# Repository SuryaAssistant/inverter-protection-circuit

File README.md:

# inverter-protection-circuit
48V inverter protection circuit

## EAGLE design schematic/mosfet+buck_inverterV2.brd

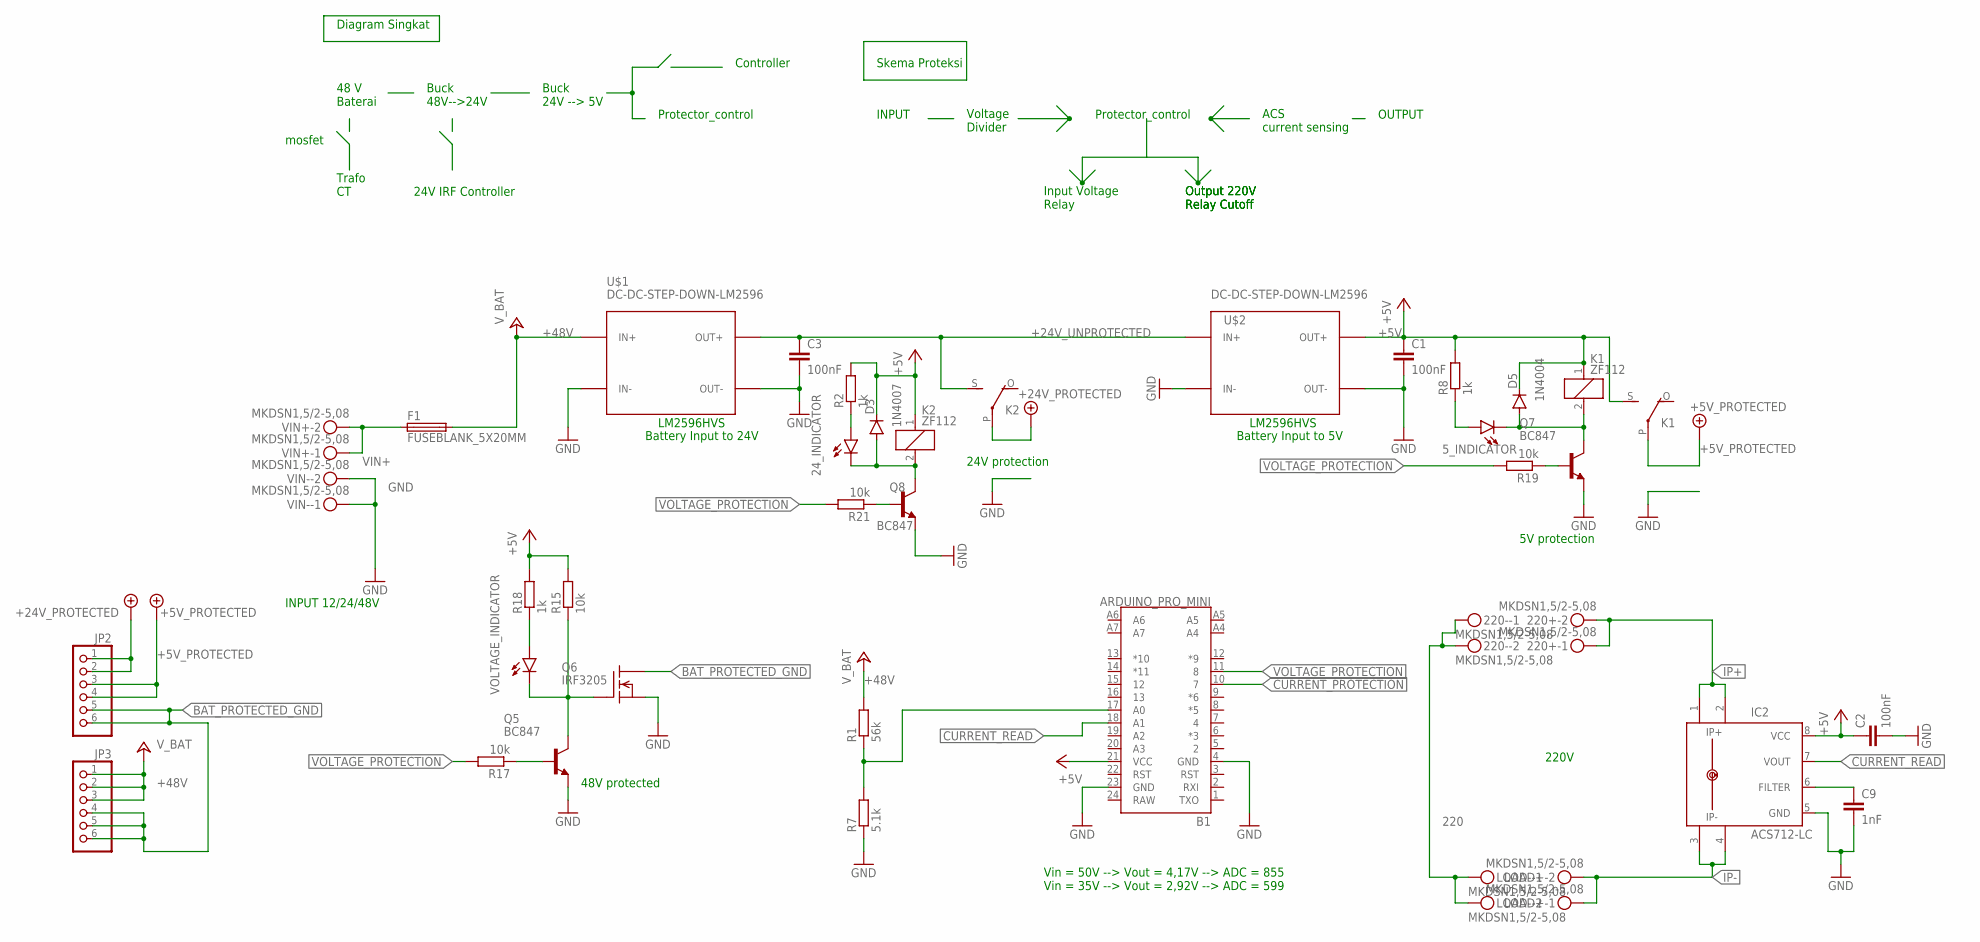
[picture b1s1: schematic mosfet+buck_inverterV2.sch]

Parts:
5_INDICATOR, 24_INDICATOR: LED1206; LED-1206
220+, 220-: MKDSN1,5/2-5,08
B1: ARDUINO_PRO_MINI
C1, C2, C3: 100nF; C0805K
C9: 1nF; C0805K
D3: 1N4007; DO41-10
D5: 1N4004; DO41-10
F1: FUSEBLANK_5X20MM; FUSE_HOLDER_5X20MM
IC2: ACS712-LC; SOIC8
JP2, JP3: PINHD-1X6CLEAN; 1X06-CLEAN
K1, K2: ZF112
LOAD+: MKDSN1,5/2-5,08
LOAD-: MKDSN1,5/2-5,08
Q5, Q7, Q8: BC847; SOT23
Q6: IRF3205; TO220
R1: 56k; R0805
R2, R8, R18: 1k; R0805
R7: 5.1k; R0805
R15, R17, R19, R21: 10k; R0805
U$1, U$2: DC-DC-STEP-DOWN-LM2596
VIN+: MKDSN1,5/2-5,08
VIN-: MKDSN1,5/2-5,08
VOLTAGE_INDICATOR: LED1206; LED-1206

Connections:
220: 220-.1, 220-.2, LOAD-.1, LOAD-.2
+5V: B1.21 (VCC), C1.1, C2.1, D3.C, D5.C, IC2.8 (VCC), K1.1, K1.S, K2.1, R2.2, R8.2, R15.2, R18.2, U$2.OUT+
+5V_PROTECTED: JP2.3, JP2.4, K1.P
+24V: JP2.1, JP2.2, K2.P
+24V_UNPROTECTED: C3.1, K2.S, U$1.OUT+, U$2.IN+
+48V: F1.2, JP3.1, JP3.2, JP3.3, R1.2, U$1.IN+
BAT_PROTECTED_GND: JP2.5, JP2.6, JP3.4, JP3.5, JP3.6, Q6.2 (D)
CURRENT_PROTECTION: B1.10 (7)
CURRENT_READ: B1.18 (A1), IC2.7 (VOUT)
GND: B1.4 (GND), B1.23 (GND), C1.2, C2.2, C3.2, C9.2, IC2.5 (GND), Q5.2 (E), Q6.3 (S), Q7.2 (E), Q8.2 (E), R7.1, U$1.IN-, U$1.OUT-, U$2.IN-, U$2.OUT-, VIN-.1, VIN-.2
IP+: 220+.1, 220+.2, IC2.1 (IP+), IC2.2 (IP+1)
IP-: IC2.3 (IP-), IC2.4 (IP-1), LOAD+.1, LOAD+.2
unnamed: B1.17 (A0), R1.1, R7.2
unnamed: 24_INDICATOR.A, R2.1
unnamed: Q5.3 (C), Q6.1 (G), R15.1, VOLTAGE_INDICATOR.C
unnamed: Q5.1 (B), R17.1
unnamed: 24_INDICATOR.C, D3.A, K2.2, Q8.3 (C)
unnamed: R18.1, VOLTAGE_INDICATOR.A
unnamed: 5_INDICATOR.C, D5.A, K1.2, Q7.3 (C)
unnamed: Q7.1 (B), R19.1
unnamed: Q8.1 (B), R21.1
unnamed: C9.1, IC2.6 (FILTER)
unnamed: 5_INDICATOR.A, R8.1
RAW: B1.24 (RAW)
VIN+: F1.1, VIN+.1, VIN+.2
VOLTAGE_PROTECTION: B1.11 (8), R17.2, R19.2, R21.2

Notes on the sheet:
INPUT 12/24/48V
Battery Input to 5V
LM2596HVS
Battery Input to 24V
Vin = 50V --> Vout = 4,17V --> ADC = 855 Vin = 35V --> Vout = 2,92V --> ADC = 599
48V protected
24V protection
5V protection
48 V Baterai
Buck 48V-->24V
Buck 24V --> 5V
Controller
Protector_control
Trafo CT
24V IRF Controller
Diagram Singkat
ACS current sensing
Voltage Divider
mosfet
OUTPUT
INPUT
Input Voltage Relay
Output 220V Relay Cutoff
Skema Proteksi
220V

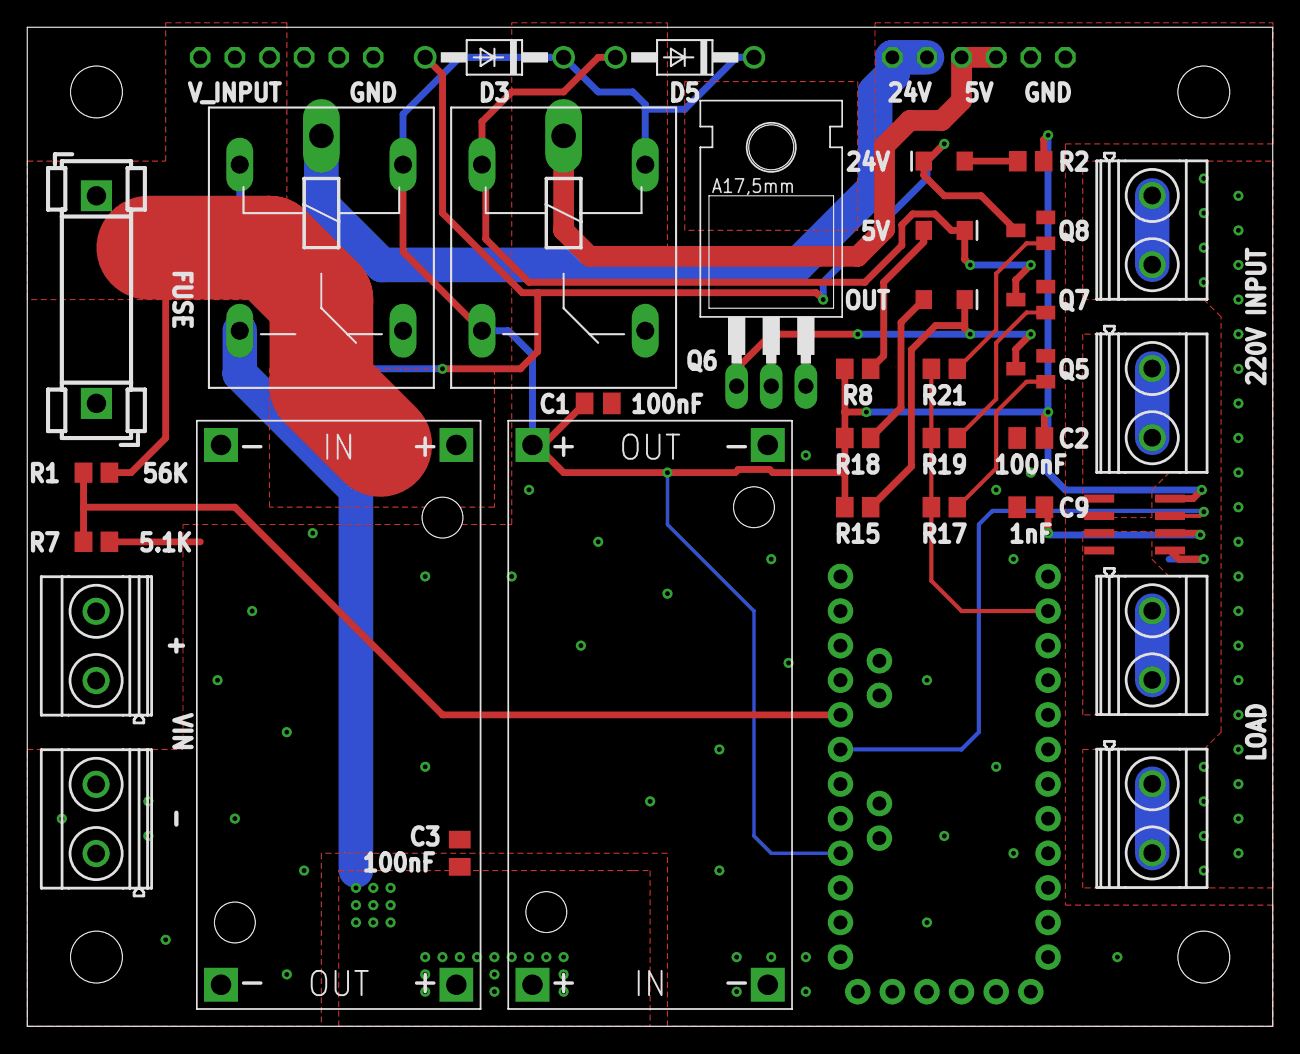
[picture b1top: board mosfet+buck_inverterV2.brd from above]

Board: 2 copper layers, 91.4 x 73.3 mm, 37 parts (0 on the bottom side), 24 nets.

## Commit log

2021-03-05 add readme
2021-03-05 add voltage protection
2021-03-05 add acs712
2021-03-05 add current limitation
2021-03-08 edit
2021-03-08 add board

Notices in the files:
parts and their libraries:
SparkFun-LED: Licensing: Creative Commons ShareAlike 4.0 International - https://creativecommons.org/licenses/by-sa/4.0
diy-modules: Released under the Creative Commons Attribution 4.0 International License: http://creativecommons.org/licenses/by/4.0
